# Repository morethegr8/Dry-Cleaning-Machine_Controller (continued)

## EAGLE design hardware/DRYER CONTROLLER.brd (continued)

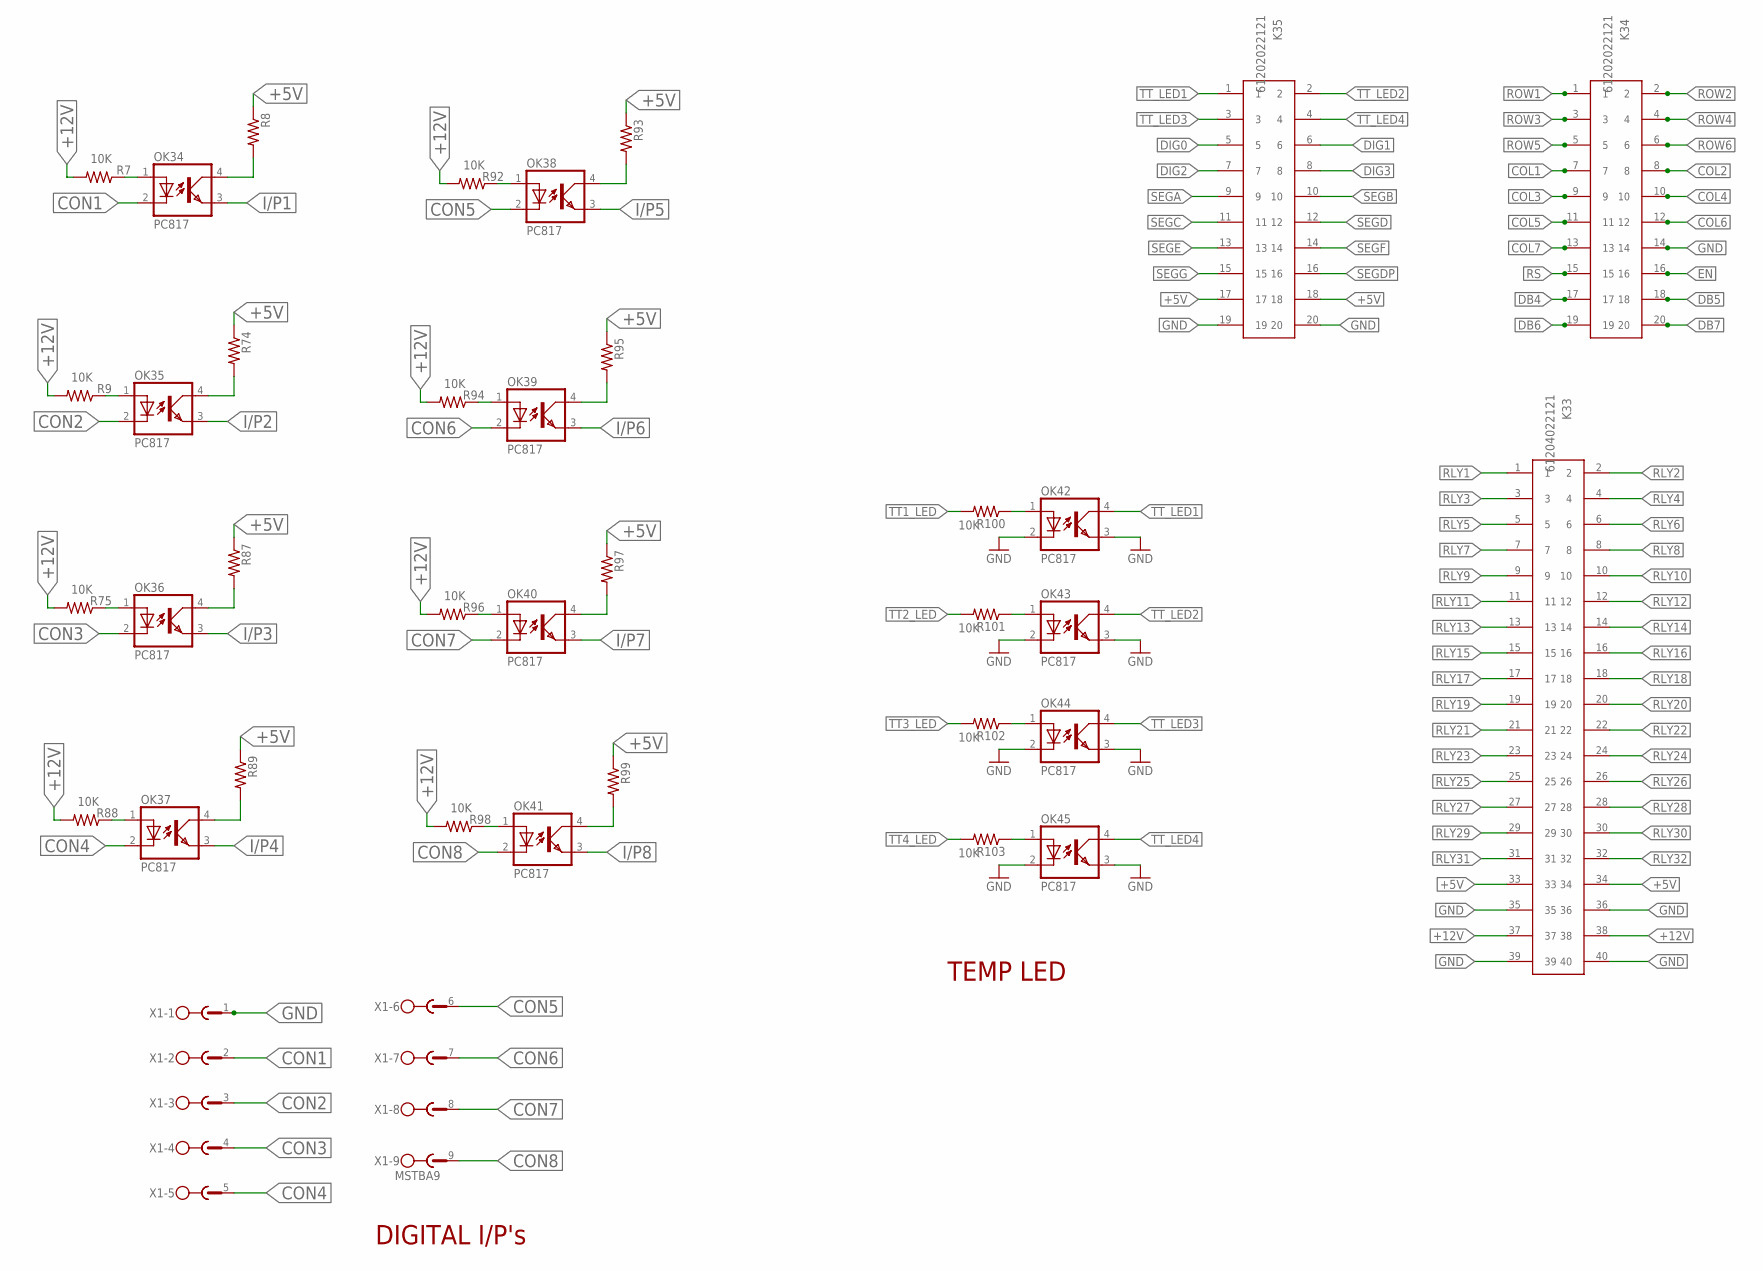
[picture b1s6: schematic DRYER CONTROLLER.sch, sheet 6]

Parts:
K33: 61204022121
K34, K35: 61202022121
OK34, OK35, OK36, OK37, OK38, OK39, OK40, OK41, OK42, OK43, OK44, OK45: PC817; DIL04
R7, R9, R75, R88, R92, R94, R96, R98, R100, R101, R102, R103: 10K; R0805
R8, R74, R87, R89, R93, R95, R97, R99: R-US_R1206; R1206
X1: MSTBA9

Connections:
+5V: K33.33, K33.34, K35.17, K35.18, R8.1, R74.1, R87.1, R89.1, R93.1, R95.1, R97.1, R99.1; also elsewhere on the board
+12V: K33.37, K33.38, R7.2, R9.2, R75.2, R88.2, R92.2, R94.2, R96.2, R98.2; also elsewhere on the board
COL1: K34.7; also elsewhere on the board
COL2: K34.8; also elsewhere on the board
COL3: K34.9; also elsewhere on the board
COL4: K34.10; also elsewhere on the board
COL5: K34.11; also elsewhere on the board
COL6: K34.12; also elsewhere on the board
COL7: K34.13; also elsewhere on the board
CON1: OK34.2 (C), X1.2
CON2: OK35.2 (C), X1.3
CON3: OK36.2 (C), X1.4
CON4: OK37.2 (C), X1.5
CON5: OK38.2 (C), X1.6
CON6: OK39.2 (C), X1.7
CON7: OK40.2 (C), X1.8
CON8: OK41.2 (C), X1.9
DB4: K34.17; also elsewhere on the board
DB5: K34.18; also elsewhere on the board
DB6: K34.19; also elsewhere on the board
DB7: K34.20; also elsewhere on the board
DIG0: K35.5; also elsewhere on the board
DIG1: K35.6; also elsewhere on the board
DIG2: K35.7; also elsewhere on the board
DIG3: K35.8; also elsewhere on the board
EN: K34.16; also elsewhere on the board
GND: K33.35, K33.36, K33.39, K33.40, K34.14, K35.19, K35.20, OK42.2 (C), OK42.3 (EMIT), OK43.2 (C), OK43.3 (EMIT), OK44.2 (C), OK44.3 (EMIT), OK45.2 (C), OK45.3 (EMIT), X1.1; also elsewhere on the board
I/P1: OK34.3 (EMIT); also elsewhere on the board
I/P2: OK35.3 (EMIT); also elsewhere on the board
I/P3: OK36.3 (EMIT); also elsewhere on the board
I/P4: OK37.3 (EMIT); also elsewhere on the board
I/P5: OK38.3 (EMIT); also elsewhere on the board
I/P6: OK39.3 (EMIT); also elsewhere on the board
I/P7: OK40.3 (EMIT); also elsewhere on the board
I/P8: OK41.3 (EMIT); also elsewhere on the board
unnamed: OK34.1 (A), R7.1
unnamed: OK35.1 (A), R9.1
unnamed: OK35.4 (COL), R74.2
unnamed: OK36.1 (A), R75.1
unnamed: OK36.4 (COL), R87.2
unnamed: OK37.1 (A), R88.1
unnamed: OK34.4 (COL), R8.2
unnamed: OK37.4 (COL), R89.2
unnamed: OK39.1 (A), R94.1
unnamed: OK39.4 (COL), R95.2
unnamed: OK40.1 (A), R96.1
unnamed: OK40.4 (COL), R97.2
unnamed: OK41.1 (A), R98.1
unnamed: OK41.4 (COL), R99.2
unnamed: OK38.1 (A), R92.1
unnamed: OK38.4 (COL), R93.2
unnamed: OK42.1 (A), R100.1
unnamed: OK43.1 (A), R101.1
unnamed: OK44.1 (A), R102.1
unnamed: OK45.1 (A), R103.1
RLY1: K33.1; also elsewhere on the board
RLY2: K33.2; also elsewhere on the board
RLY3: K33.3; also elsewhere on the board
RLY4: K33.4; also elsewhere on the board
RLY5: K33.5; also elsewhere on the board
RLY6: K33.6; also elsewhere on the board
RLY7: K33.7; also elsewhere on the board
RLY8: K33.8; also elsewhere on the board
RLY9: K33.9; also elsewhere on the board
RLY10: K33.10; also elsewhere on the board
RLY11: K33.11; also elsewhere on the board
RLY12: K33.12; also elsewhere on the board
RLY13: K33.13; also elsewhere on the board
RLY14: K33.14; also elsewhere on the board
RLY15: K33.15; also elsewhere on the board
RLY16: K33.16; also elsewhere on the board
RLY17: K33.17; also elsewhere on the board
RLY18: K33.18; also elsewhere on the board
RLY19: K33.19; also elsewhere on the board
RLY20: K33.20; also elsewhere on the board
RLY21: K33.21; also elsewhere on the board
RLY22: K33.22; also elsewhere on the board
RLY23: K33.23; also elsewhere on the board
RLY24: K33.24; also elsewhere on the board
RLY25: K33.25; also elsewhere on the board
RLY26: K33.26; also elsewhere on the board
RLY27: K33.27; also elsewhere on the board
RLY28: K33.28; also elsewhere on the board
RLY29: K33.29; also elsewhere on the board
RLY30: K33.30; also elsewhere on the board
RLY31: K33.31; also elsewhere on the board
RLY32: K33.32; also elsewhere on the board
ROW1: K34.1; also elsewhere on the board
ROW2: K34.2; also elsewhere on the board
ROW3: K34.3; also elsewhere on the board
ROW4: K34.4; also elsewhere on the board
ROW5: K34.5; also elsewhere on the board
ROW6: K34.6; also elsewhere on the board
RS: K34.15; also elsewhere on the board
SEGA: K35.9; also elsewhere on the board
SEGB: K35.10; also elsewhere on the board
SEGC: K35.11; also elsewhere on the board
SEGD: K35.12; also elsewhere on the board
SEGDP: K35.16; also elsewhere on the board
SEGE: K35.13; also elsewhere on the board
SEGF: K35.14; also elsewhere on the board
SEGG: K35.15; also elsewhere on the board
TT1_LED: R100.2; also elsewhere on the board
TT2_LED: R101.2; also elsewhere on the board
TT3_LED: R102.2; also elsewhere on the board
TT4_LED: R103.2; also elsewhere on the board
TT_LED1: K35.1, OK42.4 (COL)
TT_LED2: K35.2, OK43.4 (COL)
TT_LED3: K35.3, OK44.4 (COL)
TT_LED4: K35.4, OK45.4 (COL)

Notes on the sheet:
DIGITAL I/P's
TEMP LED

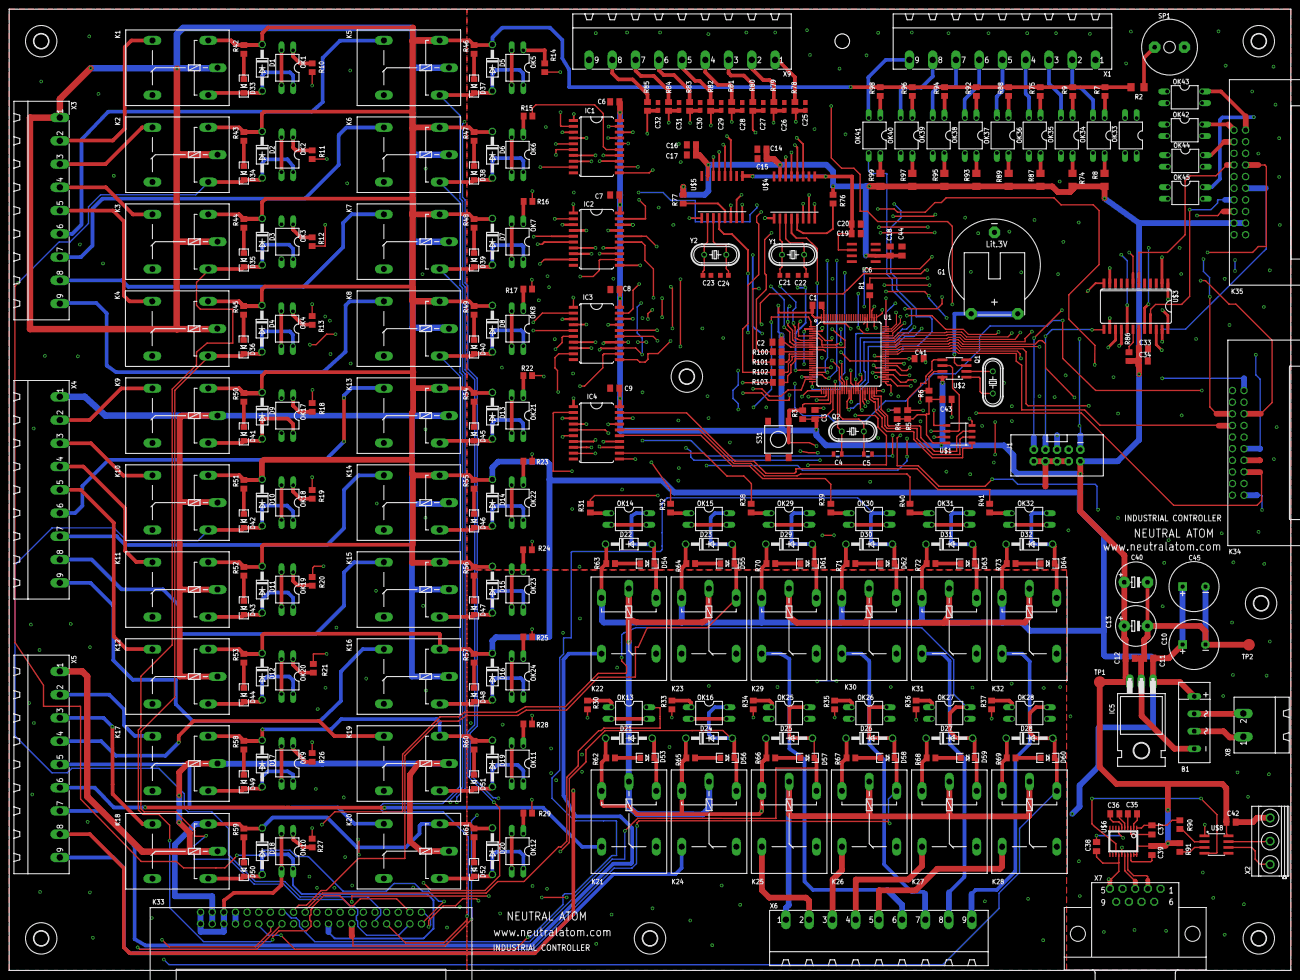
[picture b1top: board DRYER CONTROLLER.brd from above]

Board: 4 copper layers, 280.0 x 210.0 mm, 335 parts (1 on the bottom side), 323 nets.

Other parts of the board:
DRILEGEND: DRILEGEND

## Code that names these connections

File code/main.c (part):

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########################PIN DEFINITION############################################
	LCD - 4 bit mode
	DATA PINS - DB4~DB7 - PORTG PIN 2~5
	EN - PG1
	RS - PG0 
#################################################################################
	Matrix Keyboard - 6 ROWS X 7 COLUMNS - PORTE & PORTJ
	Buzzer - PJ7
#########################################################
	UART
	RX - PE0
	TX - PE1
########################################################
	EEPROM - PORTD
	ADDRESS BUS - 
	A0 - PD4
	A1 - PD5
	A2 - PD6
	WP - PD7
#########################################################
	OCTAL DATA LATCH - ADDRESS BUS - PORTA PIN 0~7
	LATCH ENABLE & LATCH OC - PORTC - PIN 0~7
	OC1 - PC4
	ENC1- PC0
	OC2 - PC5
	ENC2 - PC1
	OC3 - PC6
	ENC3 - PC2
	OC4 - PC7
	ENC4 - PC3
##########################################################
	I2C Interface - PORTD 
	SDA - PD0
	SCL - PD1
	DEVICES CONNECTED ON I2C 
	# RTC 
	# EEPROM
#########################################################
	SPI Interface - PORTB
	MISO - PB3
	MOSI - PB2
	DEVICE CONNECTED ON SPI
	# AD7705 2 Nos.
	# MAX7219
	CHIP SELECTS
	T1_SS - PB4
	T2_SS - PB5
	LDRV_SS - PB0
#########################################################
	TEMP LED - PORTH
	TT1_LED - PH0
	TT2_LED - PH1
	TT3_LED - PH2
	TT4_LED - PH3
#########################################################
	INPUTS
	RTC - SQW OUT - PD2
	DIGI INPUTS - PORTL
	I/P1~8 - PL0~PL7 

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	for (uint8_t i=0;i<10;i++)
	{
		//LED ON
		PORTJ|=(1<<PJ7);
		//~0.1s delay
		_delay_ms(20);
		//LED OFF
		PORTJ&=~(1<<PJ7);
		_delay_ms(80);
	}
}
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				if(menu_key==31)
				{
					BUZZOFF=1;
					PORTJ=(0<<PJ7);
				}
				
				if(BUZZOFF!=1)
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									lcd_number_write(dly,10);
									lcd_write_character_4d(' ');
									_delay_ms(80);                     // LOADING COUNTDWN 10 SEC
									PORTJ ^= _BV(PJ7);
									
								} while (!dly==0);
								
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								lcd_number_write(dly,10);
								lcd_write_character_4d(' ');
								_delay_ms(80);                     // LOADING COUNTDWN 10 SEC
								 PORTJ ^= _BV(PJ7);
								
							} while (!dly==0);
							
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							 lcd_write_character_4d(' ');
							 _delay_ms(80);                     // LOADING COUNTDWN 10 SEC
							  dly--;
							  PORTJ ^= _BV(PJ7);
							 //Buzz1S();
							 
						 } while (!dly==0);
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					 lcd_number_write(dly,10);
					 lcd_write_character_4d(' ');
					 _delay_ms(80);                     // LOADING COUNTDWN 10 SEC
					 PORTJ ^= _BV(PJ7);
				 
				 } while (!dly==0);
			 
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			 lcd_number_write(dly,10);
			 lcd_write_character_4d(' ');
			 _delay_ms(80);                     // LOADING COUNTDWN 10 SEC
			 PORTJ ^= _BV(PJ7);
			 
		 } while (!dly==0);
		 
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			  lcd_number_write(dly,10);
			  lcd_write_character_4d(' ');
			  _delay_ms(80);                     // LOADING COUNTDWN 10 SEC
			  PORTJ ^= _BV(PJ7);
			  
		  } while (!dly==0);
		  
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			 lcd_number_write(dly,10);
			 lcd_write_character_4d(' ');
			 _delay_ms(80);                     // LOADING COUNTDWN 10 SEC
			 PORTJ ^= _BV(PJ7);
			 
		 } while (!dly==0);
		 
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					 lcd_number_write(dly,10);
					 lcd_write_character_4d(' ');
					 _delay_ms(80);                     // LOADING COUNTDWN 10 SEC
					 PORTJ ^= _BV(PJ7);
					 
				 } while (!dly==0);
				 
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					 lcd_number_write(dly,10);
					 lcd_write_character_4d(' ');
					 _delay_ms(80);                     // LOADING COUNTDWN 10 SEC
					 PORTJ ^= _BV(PJ7);
					 
				 } while (!dly==0);
				 
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	_delay_us(10);
	DDRH=0xFF;                                                      // TEMP LEDS
	_delay_us(10);
	DDRJ=(1<<PINJ7);													//BUZZ 7, COL 6~0
	_delay_us(10);
	DDRK=0xFF;														// DNC
	_delay_us(10);
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
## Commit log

2018-12-13 Backlink to CADLAB.io has been added.
